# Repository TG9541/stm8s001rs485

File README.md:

# A small STM8S001 Break-Out Board with RS485 and DS1621S Thermometer

This KiCad project provides a small PCB with an STM8S001J3M3, a RS485 interface and a DS1621S temperature sensor. Applications include [MODBUS with STM8 eForth](https://github.com/TG9541/stm8ef-modbus).

Here is a photo of an assembled board, together with the [RS485-CH340E dongle](https://github.com/TG9541/rs485-ch340e):

The STM8S001J3M3 is a member of the "STM8S Low Density" family that's based on the "STM8S Access Line" cross-breed STM8S903, which, compared with the STM8S003, has some ([undocumented](https://github.com/TG9541/stm8ef/wiki/STM8-Low-Density-Devices#stm8s001j3)) features.

The board is supported by [STM8 eForth](https://github.com/TG9541/stm8ef/) which means that it runs an interactive development system on the chip: the serial interface for the console can either use RS485, or a two-wire interface on the GPIO PC5.

A µC with merrily 5 GPIO pins is a good shield against feature creep, but the following things "had" to be included:

* most GPIOs, including the I2C bus (PB4 & PB5), and an analog input or timer output (PC5) and the are available on 6 pin header
* a narrow PCB for a cylindrical sensors with a diameter of 7mm
* 5V nominal supply, internal 3.3V power supply with an LDO regulator
* signalling LEDs for RS485 activity (RxTx) and direction (Tx)
* 120R termination optional 

Care should be taken not to exceed 6V input supply voltage. The internal 3.3V power supply is accssible on header pin J2.1 - according to the XC6206 datasheet the maximum current is 150mA.

## Design

The design is simple: The STM8S001J3 controls the direction of the SP3485 RS485 transceivr with PA1/PD6. R3 makes sure that the SWIM interface is still usable when the SP3485 is in receive mode (i.e. listening for RS485 communication).

LED D1 indicates RS485 communcation direction "transmit". LED D2 pulsing indecates bus activity in both directions where bright pulses indicates "read" and dim pulses "write". R4 is the (optional) RS485 termination resistor.

The BOM is in the docs folder.

## Pin Headers

Pin headers are also optional: they allow the board to be used as a module for quickly building a MODBUS node with a "perfboard" (using I2C or GPIOs), but connecting wires directly is also an intended use case.

### Description Header J1
Pin|Signal
-|-
1|3.4 to 6V for XC6206 3.3V LDO regulator
2|GND
3|RS485 "A"
4|RS485 "B"

### Description Header J2
Pin|Tag|Pin STM8S001|GPIO|Features
-|-|-|-|-
1|3.3|4|VDD|3.3V from LDO regulator
2||8|PC6 | SPI_MOSI, [TIM1_CH1]
2|SWIM|8|PD1 | **SWIM**
2||8|PD3 | TIM2_CH2, TIM2_CH2, ADC_ETR
2||8|PD5 | **UART1_TX**, AIN5
3||5|PA3 | TIM2_CH3, [SPI_NSS], [UART1_TX]
3|SDA|5|PB5 | **I2C_SDA**
4||7|PC3 | TIM1_CH3, [TLI], [TIM1_CH1N]
4||7|PC4 | TIM1_CH4, CLK_CCO, AIN2, [TIM1_CH3]
4|PC5|7|PC5 | SPI_SCK, [TIM2_CH1]
5|SCL|6|PB4 | **I2C_SCL**, [ADC_ETR]
6|GND|2|VSS|GND

## PCB and Assembly

Components occupy both sides of a PCB of 33.4mm x 1/4" (the minimal width supported by Oshpark).

On the front side there is the STM8S001J3M3, a XC6206 3.3V LDO regulator, some passive components, and the RS485 signalling LEDs:

A generic 3.3V RS485 transceiver (like SP3485 or MAX3485l) and the (optional) DS1621S thermometer chip are on the backside:

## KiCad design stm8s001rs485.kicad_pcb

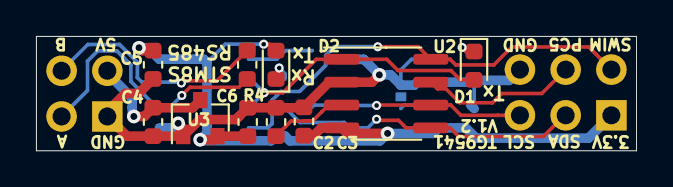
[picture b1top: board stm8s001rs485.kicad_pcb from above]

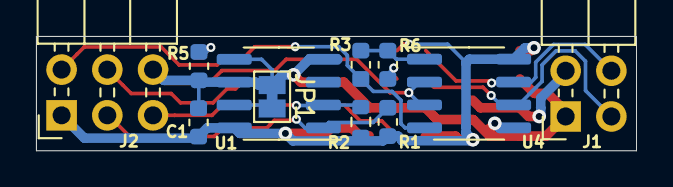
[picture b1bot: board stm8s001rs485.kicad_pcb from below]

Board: 2 copper layers, 33.3 x 6.3 mm, 21 parts (11 on the bottom side), 15 nets.

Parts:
C1, C3, C5: 100nF; C_0603_1608Metric
C2, C4, C6: 1uF; C_0603_1608Metric
D1: LED red; LED_0603_1608Metric
D2: LED green; LED_0603_1608Metric
J1: Conn_02x02_Odd_Even; PinHeader_2x02_P2.54mm_Horizontal
J2: Conn_02x03_Counter_Clockwise; PinHeader_2x03_P2.54mm_Horizontal
JP1: A0; SolderJumper-2_P1.3mm_Bridged_Pad1.0x1.5mm
R1, R2, R3, R5, R6: 4k7; R_0603_1608Metric
R4: 120R; R_0603_1608Metric
U1: DS1621S; SOIC-8_3.9x4.9mm_P1.27mm
U2: STM8S001J3M; SOIC-8_3.9x4.9mm_P1.27mm
U3: XC6206P332MR; SOT-23
U4: SP3485CN; SOIC-8_3.9x4.9mm_P1.27mm

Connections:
+3V3: C1.2, C3.2, C5.2, C6.2, D2.2, J2.1, R1.1, R2.1, U1.8, U2.4, U3.2, U4.8
+5V: C4.2, J1.2, U3.3
/A: J1.3, R4.1, U4.6
/B: J1.4, R4.2, U4.7
/DIR.RX: D1.2, U2.1, U4.2, U4.3
/PC5: J2.4, U2.7
/SCL: J2.5, R2.2, U1.2, U2.6
/SDA: J2.3, R1.2, U1.1, U2.5
/SWIM.TX: J2.2, R3.1, U2.8, U4.4
GND: C1.1, C2.1, C3.1, C4.1, C5.1, C6.1, J1.1, J2.6, JP1.1, R5.2, U1.4, U1.5, U1.6, U2.2, U3.1, U4.5
unnamed: C2.2, U2.3
unnamed: D1.1, R5.1
unnamed: D2.1, R6.1
unnamed: JP1.2, U1.7
unnamed: R3.2, R6.2, U4.1

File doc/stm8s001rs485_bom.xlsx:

Source: | /home/thomas/kicad/stm8s001rs485/stm8s001rs485.sch
Date: | Sa 31 Aug 2019 14:30:23 CEST
Tool: | Eeschema 5.1.4-e60b266~84~ubuntu16.04.1
Generator: | /usr/share/kicad/plugins/bom_csv_grouped_by_value_with_fp.py
Component Count: | 20
Ref | Qnty | Value | Cmp name | Footprint | Description | Vendor
C2, C4, C6, | 3 | 1uF | C | Capacitor_SMD:C_0603_1608Metric | Unpolarized capacitor
C3, C1, C5, | 3 | 100nF | C | Capacitor_SMD:C_0603_1608Metric | Unpolarized capacitor
D1, | 1 | LED red | LED | LED_SMD:LED_0603_1608Metric | Light emitting diode
D2, | 1 | LED green | LED | LED_SMD:LED_0603_1608Metric | Light emitting diode
J1, | 1 | Conn_02x02_Odd_Even | Conn_02x02_Odd_Even | Connector_PinHeader_2.54mm:PinHeader_2x02_P2.54mm_Horizontal | Generic connector, double row, 02x02, odd/even pin numbering scheme (row 1 odd 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
J2, | 1 | Conn_02x03_Counter_Clockwise | Conn_02x03_Counter_Clockwise | Connector_PinHeader_2.54mm:PinHeader_2x03_P2.54mm_Horizontal | Generic connector, double row, 02x03, counter clockwise pin numbering scheme (s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
R1, R2, R5, R6, R3, | 5 | 4k7 | R | Resistor_SMD:R_0603_1608Metric | Resistor
R4, | 1 | 120R | R | Resistor_SMD:R_0603_1608Metric | Resistor
U1, | 1 | DS1621S | DS1621S | Package_SO:SOIC-8_3.9x4.9mm_P1.27mm | 1-Wire Digital Thermometer and Thermostat, SOIC-8
U2, | 1 | STM8S001J3M | STM8S001J3M | Package_SO:SOIC-8_3.9x4.9mm_P1.27mm | 16MHz, 8K Flash, 1K RAM, 128 EEPROM, SO-8
U3, | 1 | XC6206P332MR | XC6206P332MR | Package_TO_SOT_SMD:SOT-23 | Low Quiescent Current LDO Regulator, 3.3V, 200 mA, Vin<=7V, SOT-23
U4, | 1 | SP3485CN | SP3485CN | Package_SO:SOIC-8_3.9x4.9mm_P1.27mm | 3.3V Low Power Half-Duplex RS-485 Transceiver 10Mbps, SO8

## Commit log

2019-08-31 Files according to first Oshpark order
2019-08-31 BOM added
2019-08-31 Docs improved
2019-08-31 Improved docs
2019-10-11 Improved component placement
2019-10-13 Aligned 3.3V vias
2019-10-13 V1.1 improved component placement
2021-02-06 improved RX/TX LED
